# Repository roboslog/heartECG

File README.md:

# heartECG
The most powerful AI-based ECG device called heartslog not only heart function but also include many important parameters like Heart rate, Blood pulse ,pulse oximetry ,glucometer

With AI startup - www.tantrabyte.org, We are building the most powerful AI-based ECG device called heartslog not only heart function but also include many important parameters...  
	•	Heart rate
	•	Blood pulse
	•	Pulse oximetry
	•	glucometer
	•	energy
Much more predictions, AI/ML/ Deep Learning...Work 
For any suggestion/work DM - info@tantabyte.org 
we highly appreciate your time.  WhatsApp - https://wa.me/919205137675

Our all files & Code here are For Non-Commercial (Educational) use Only, For Commercial Use: Give Credit to ROBOSLOG & Tantrabyte
Thanks
More updates coming soon..

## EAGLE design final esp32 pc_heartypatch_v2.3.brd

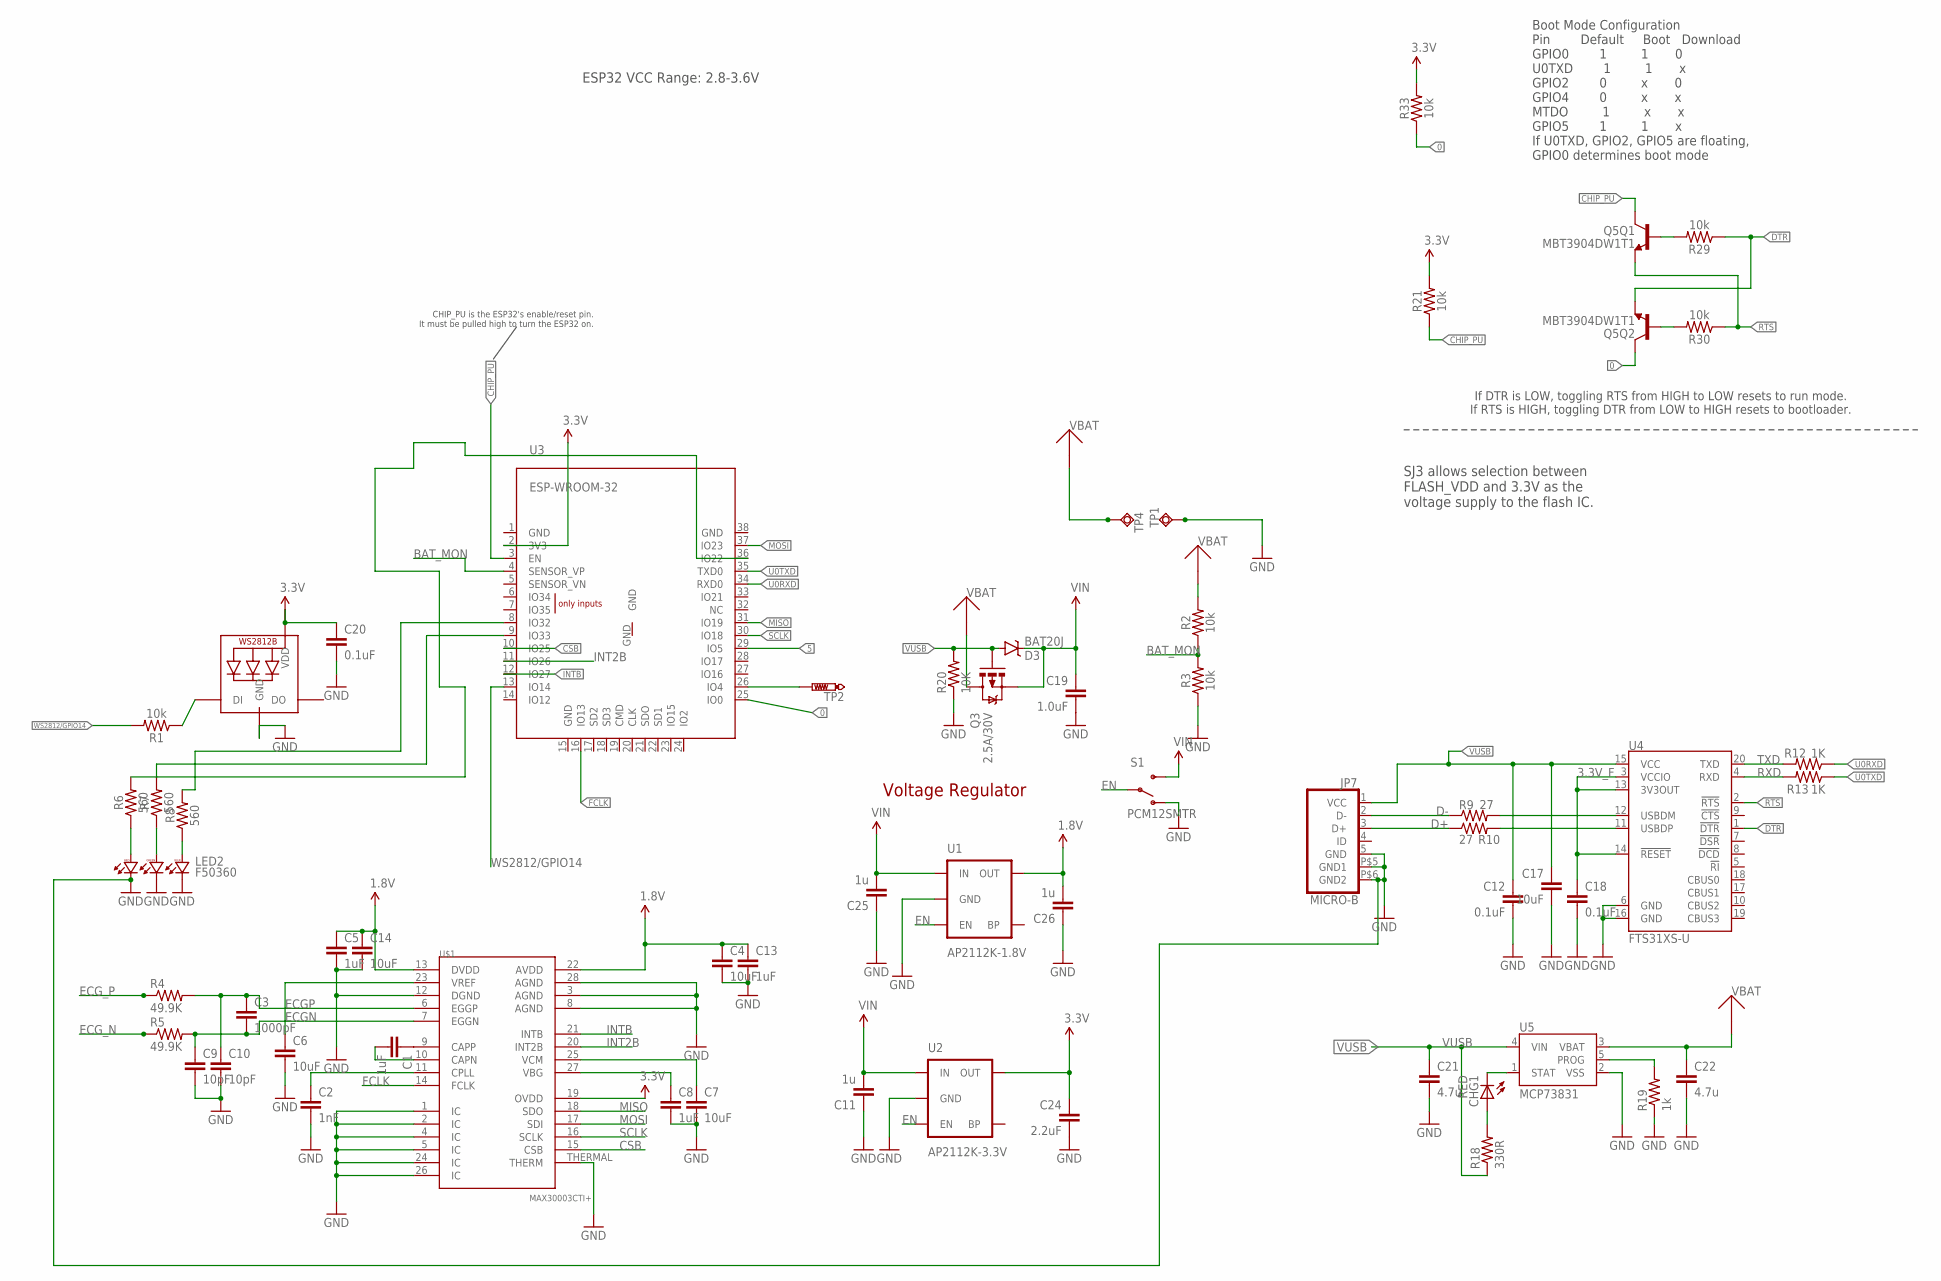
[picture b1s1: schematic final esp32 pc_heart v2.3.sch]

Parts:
C1: 1uF; C0603
C2: 1nF; C0603
C3: 1000pF; C0402
C4, C6, C7, C17: 10uF; C0805
C5: 1uF; C0402
C8, C13: 1uF; C0805
C9, C10: 10pF; C0402
C11, C25, C26: 1u; C0402
C12, C18: 0.1uF; C0402
C14: 10uF; C0603
C19: 1.0uF; C0402
C20: 0.1uF; 0603
C21, C22: 4.7u; C0805
C24: 2.2uF; C0603
CHG1: RED; CHIPLED_0603
D3: BAT20J; SOD-323
JP7: MICRO-B
LED1: WS2812B5050; WS2812B
LED2: F50360
Q3: 2.5A/30V; SOT23-3
Q5: MBT3904DW1T1; SC70-6
R1, R2, R3, R21, R29, R30, R33: 10k; 0603
R4, R5: 49.9K; 0805
R6, R7, R8: 560; 0603
R9, R10: 27; R0402
R12, R13: 1K; R0402
R18: 330R; R0402
R19: 1k; R0402
R20: 10K; R0402
S1: PCM12SMTR; SWITCH-SPST-SMD-A
TP1, TP4: TPSQTP20SQ; TP20SQ
TP2: PTR1TP10SQ; TP10SQ
U1: AP2112K-1.8V; SOT23-5
U2: AP2112K-3.3V; SOT23-5
U3: ESP-WROOM-32
U4: FTS31XS-U; SSOP20_L
U5: MCP73831; SOT23-5
U$1: MAX30003CTI+; QFN-28

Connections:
0: Q5.6 (C), R33.1, U3.25 (IO0)
1.8V: C4.1, C5.1, C13.1, C14.1, C26.2, U1.5 (OUT), U$1.13 (DVDD), U$1.22 (AVDD)
3.3V: C20.1, C24.1, LED1.1-VDD (VDD), R21.2, R33.2, U2.5 (OUT), U3.2 (3V3), U$1.19 (OVDD)
3.3V_F: C18.1, U4.3 (VCCIO), U4.13 (3V3OUT), U4.14 (!RESET)
5: U3.29 (IO5)
BAT_MON: R2.1, R3.2, U3.4 (SENSOR_VP)
CHIP_PU: Q5.3 (C), R21.1, U3.3 (EN)
CSB: U3.10 (IO25), U$1.15 (CSB)
D+: JP7.3 (D+), R10.1
D-: JP7.2 (D-), R9.1
DTR: Q5.1 (E), R29.1, U4.1 (!DTR)
ECGN: C3.2, C9.1, R5.2, U$1.7 (EGGN)
ECGP: C3.1, C10.1, R4.2, U$1.6 (EGGP)
ECG_N: R5.1
ECG_P: R4.1
EN: S1.2, U1.3 (EN), U2.3 (EN)
FCLK: U3.16 (IO13), U$1.14 (FCLK)
GND: C2.2, C4.2, C5.2, C6.2, C7.2, C8.2, C9.2, C10.2, C11.1, C12.2, C13.2, C14.2, C17.2, C18.2, C19.2, C20.2, C21.2, C22.2, C24.2, C25.1, C26.1, JP7.5 (GND), JP7.P$5 (GND1), JP7.P$6 (GND2), LED1.3-GND (GND), LED2.BC, LED2.GC, LED2.RC, R3.1, R19.1, R20.1, S1.1 (O), TP1.TP, U1.2 (GND), U2.2 (GND), U4.6 (GND), U4.16 (GND), U5.2 (VSS), U$1.1 (IC), U$1.2 (IC), U$1.3 (AGND), U$1.4 (IC), U$1.5 (IC), U$1.8 (AGND), U$1.12 (DGND), U$1.24 (IC), U$1.26 (IC), U$1.28 (AGND), U$1.THERMAL (THERM)
INT2B: U3.11 (IO26), U$1.20 (INT2B)
INTB: U3.12 (IO27), U$1.21 (INTB)
MISO: U3.31 (IO19), U$1.18 (SDO)
MOSI: U3.37 (IO23), U$1.17 (SDI)
unnamed: LED1.4-DIN (DI), R1.1
unnamed: C6.1, U$1.23 (VREF)
unnamed: C1.1, U$1.9 (CAPP)
unnamed: TP2.TP, U3.26 (IO4)
unnamed: CHG1.C, U5.1 (STAT)
unnamed: C1.2, U$1.10 (CAPN)
unnamed: C2.1, U$1.11 (CPLL)
unnamed: R9.2, U4.12 (USBDM)
unnamed: LED2.RA, R6.1
unnamed: R10.2, U4.11 (USBDP)
unnamed: R7.2, U3.9 (IO33)
unnamed: C7.1, U$1.25 (VCM)
unnamed: C8.1, U$1.27 (VBG)
unnamed: LED2.BA, R8.1
unnamed: CHG1.A, R18.2
unnamed: LED2.GA, R7.1
unnamed: R19.2, U5.5 (PROG)
unnamed: R8.2, U3.8 (IO32)
unnamed: R6.2, U3.36 (IO22)
unnamed: Q5.5 (B), R29.2
unnamed: Q5.2 (B), R30.2
RTS: Q5.4 (E), R30.1, U4.2 (!RTS)
RXD: R13.2, U4.4 (RXD)
SCLK: U3.30 (IO18), U$1.16 (SCLK)
TXD: R12.2, U4.20 (TXD)
U0RXD: R12.1, U3.34 (RXD0)
U0TXD: R13.1, U3.35 (TXD0)
VBAT: C22.1, Q3.3 (D), R2.2, TP4.TP, U5.3 (VBAT)
VIN: C11.2, C19.1, C25.2, D3.C, Q3.2 (S), S1.3 (S), U1.1 (IN), U2.1 (IN)
VUSB: C12.1, C17.1, C21.1, D3.A, JP7.1 (VCC), Q3.1 (G), R18.1, R20.2, U4.15 (VCC), U5.4 (VIN)
WS2812/GPIO14: R1.2, U3.13 (IO14)

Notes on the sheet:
Boot Mode Configuration Pin Default Boot Download GPIO0 1 1 0 U0TXD 1 1 x GPIO2 0 x 0 GPIO4 0 x x MTDO 1 x x GPIO5 1 1 x If U0TXD, GPIO2, GPIO5 are floating, GPIO0 determines boot mode
ESP32 VCC Range: 2.8-3.6V
SJ3 allows selection between FLASH_VDD and 3.3V as the voltage supply to the flash IC.
If DTR is LOW, toggling RTS from HIGH to LOW resets to run mode. If RTS is HIGH, toggling DTR from LOW to HIGH resets to bootloader.
CHIP_PU is the ESP32's enable/reset pin. It must be pulled high to turn the ESP32 on.
Voltage Regulator

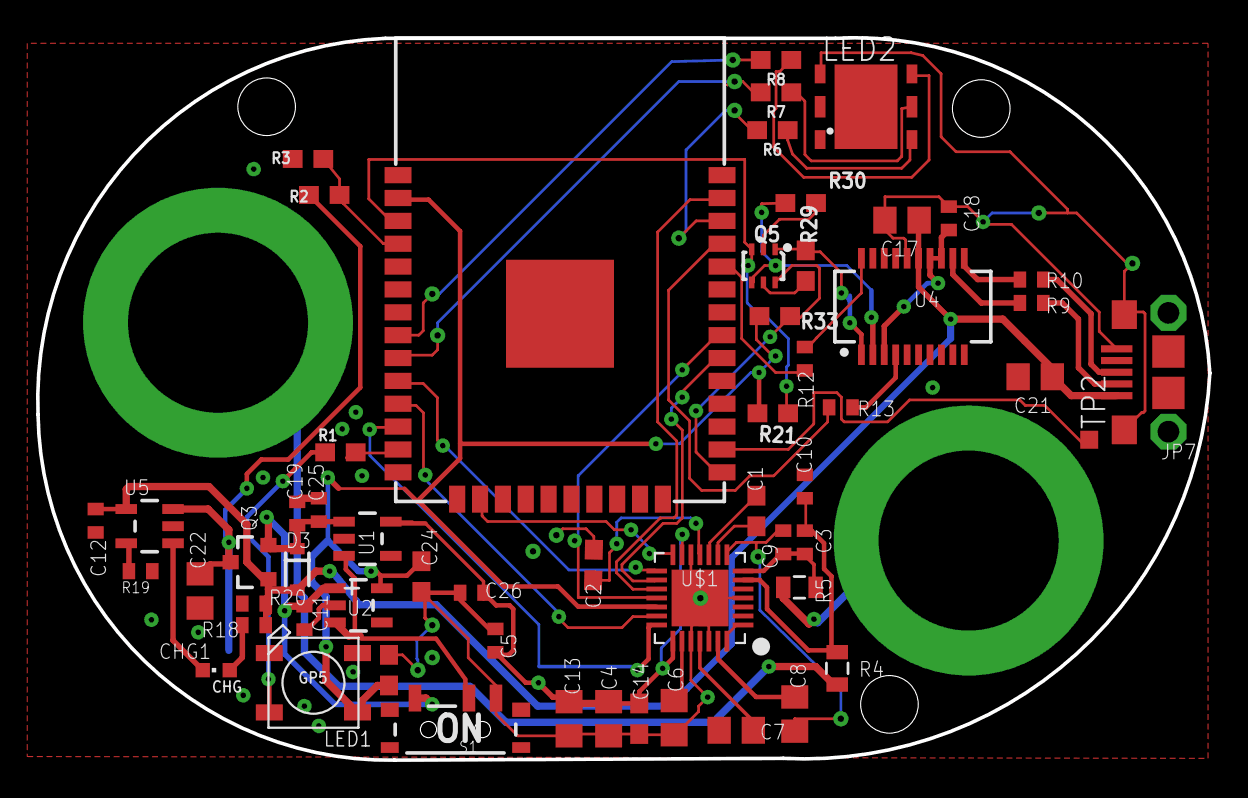
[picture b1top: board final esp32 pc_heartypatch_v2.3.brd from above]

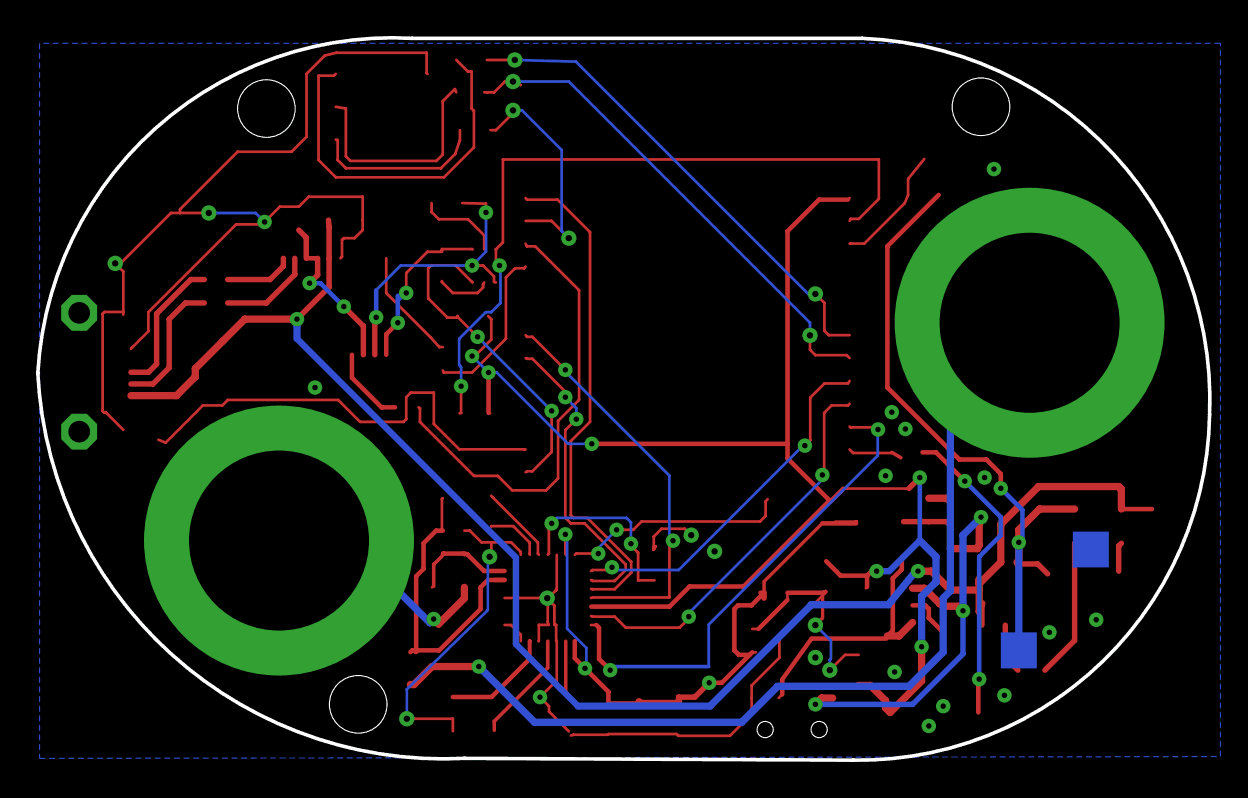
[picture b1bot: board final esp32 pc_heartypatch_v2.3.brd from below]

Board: 2 copper layers, 65.1 x 40.1 mm, 59 parts (2 on the bottom side), 50 nets.

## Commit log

2020-05-23 Rename final esp32 pc_heartypatch_v2.3.brd to pcb/final esp32 pc_heart v2.3.brd
2020-05-23 Rename final esp32 pc_heartypatch_v2.3.sch to pcb/final esp32 pc_heart v2.3.sch
2020-05-23 Rename final esp32 pc_heart v1.3.brd to pcb/esp32 pc_heart v1.3.brd
2020-05-23 Rename final esp32 pc_heart v1.3.sch to pcb/esp32 pc_heart v1.3.sch

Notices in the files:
parts and their libraries:
SparkFun-Aesthetics: Licensing: Creative Commons ShareAlike 4.0 International - https://creativecommons.org/licenses/by-sa/4.0
SparkFun-DigitalIC: Licensing: CC v3.0 Share-Alike You are welcome to use this library for commercial purposes.
